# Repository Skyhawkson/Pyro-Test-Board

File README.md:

# Pyro-Test-Board
An analog, high-current pyrotechnic driver for evaluating high power rocketry igniters

This board is intended to evaluate igniters and other pyrotechnic devices used in high-power rocketry for safe parachute ejection. It uses closed-loop analog current control to drive a set current through a device of varying resistance while allowing for external measurements of the test device's performance. It is intended for benchtop use with a 3S or 4S LiPo battery, or a benchtop power supply. 

More information can be found in the [Schematic](https://github.com/Skyhawkson/Pyro-Test-Board/blob/main/Pyro%20Tester%20Rev1.0.0/Pyro%20Test%20Board.pdf) or the [KiCAD 7+ Project Files](https://github.com/Skyhawkson/Pyro-Test-Board/tree/main/Pyro%20Tester%20Rev1.0.0/Pyro%20Test%20Board%20Rev1.0.0).
SPICE simulation data is located in the [SPICE Sims](https://github.com/Skyhawkson/Pyro-Test-Board/tree/main/Pyro%20Tester%20Rev1.0.0/SPICE%20Sims) folder.

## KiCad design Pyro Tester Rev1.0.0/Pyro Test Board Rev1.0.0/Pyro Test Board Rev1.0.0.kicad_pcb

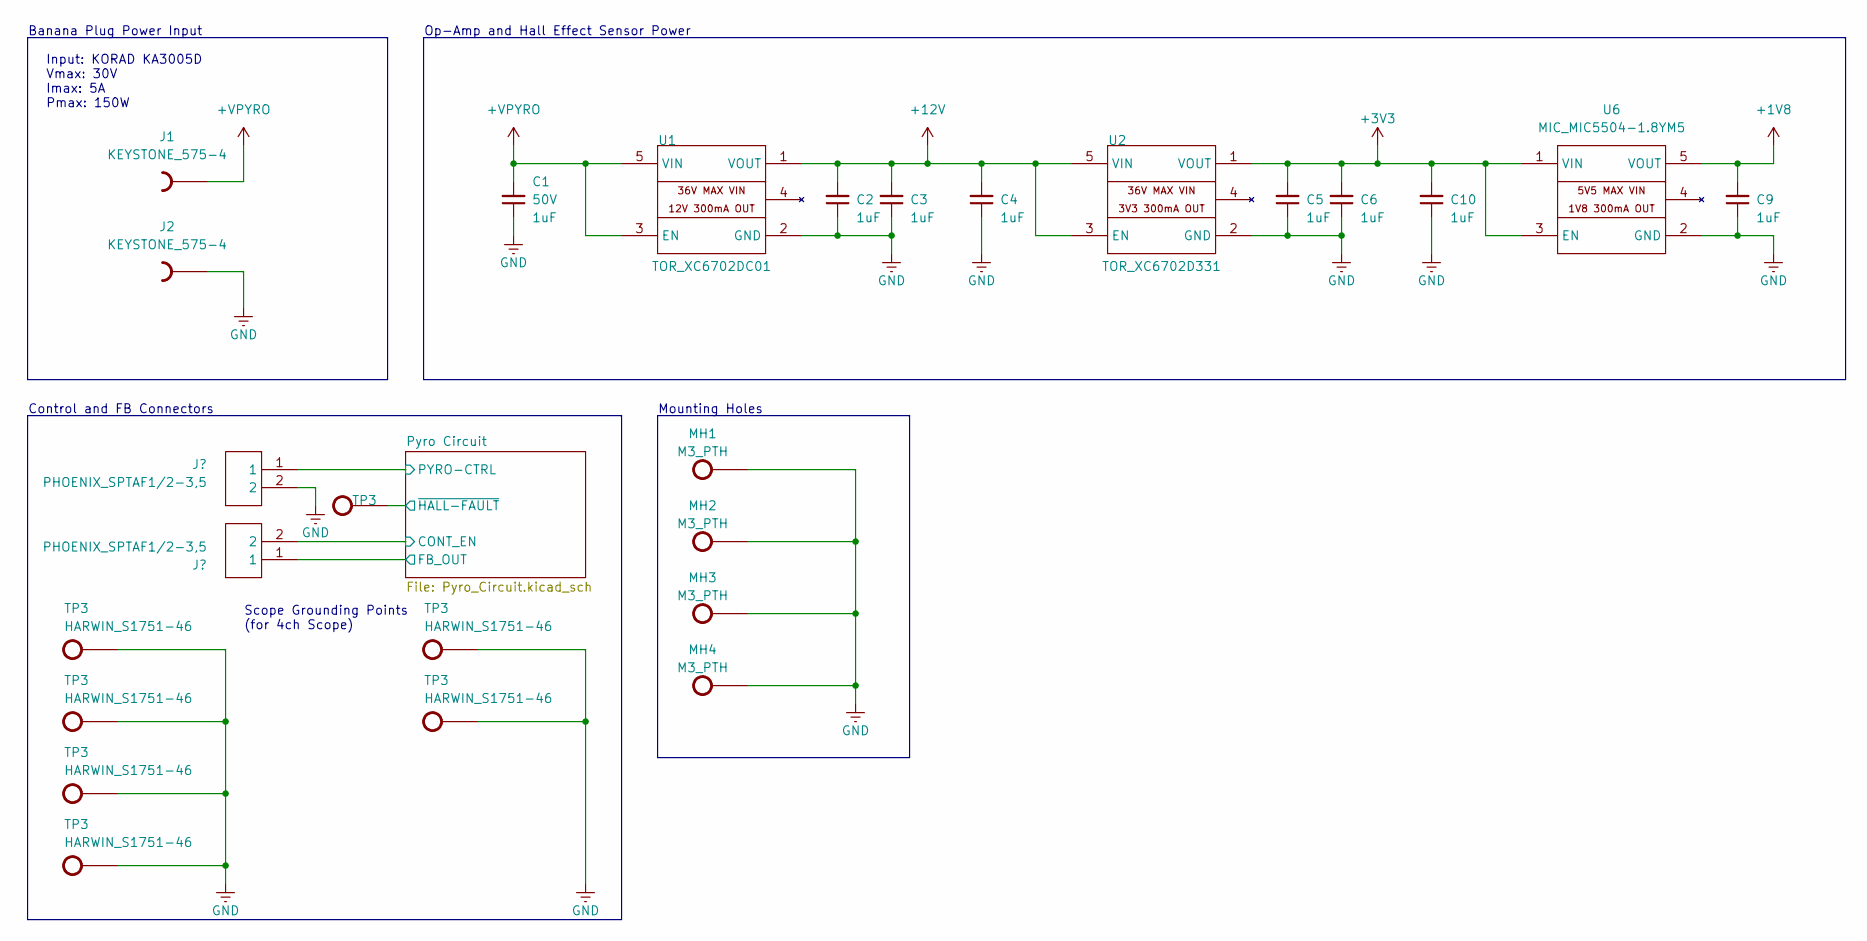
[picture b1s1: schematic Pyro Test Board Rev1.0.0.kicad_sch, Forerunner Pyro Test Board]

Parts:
C1, C2, C3, C4, C5, C6, C9, C10: 1UF_0805; GENERIC_0805_CAP; Tolerance 10%; Rating 50V
J1, J2: KEYSTONE_575-4
J3, J4: PHOENIX_SPTAF1/2-3,5; PHOENIX_SPTAF1_2-3,5
MH1, MH2, MH3, MH4: M3_PTH; GENERIC_MH_M3
TP3: HARWIN_S1751-46; HARWIN_S1751-XX
U1: TOR_XC6702DC01; TOR_SOT-89-5
U2: TOR_XC6702D331; TOR_SOT-89-5
U6: MIC_MIC5504-1.8YM5; MIC_SOT23-5LD-PL-1

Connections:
+1V8: C9.2, U6.5 (VOUT); also elsewhere on the board
+3V3: C5.2, C6.2, C10.2, U2.1 (VOUT), U6.1 (VIN), U6.3 (EN); also elsewhere on the board
+12V: C2.2, C3.2, C4.2, U1.1 (VOUT), U2.3 (EN), U2.5 (VIN); also elsewhere on the board
+VPYRO: C1.2, J1.1, U1.3 (EN), U1.5 (VIN); also elsewhere on the board
/Pyro Circuit/CONT_EN: J4.2, J4.2B; also elsewhere on the board
/Pyro Circuit/FB_OUT: J4.1, J4.1B; also elsewhere on the board
/Pyro Circuit/PYRO-CTRL: J3.1, J3.1B; also elsewhere on the board
GND: C1.1, C2.1, C3.1, C4.1, C5.1, C6.1, C9.1, C10.1, J2.1, J3.2, J3.2B, MH1.1, MH2.1, MH3.1, MH4.1, TP3.1, U1.2 (GND), U2.2 (GND), U6.2 (GND); also elsewhere on the board

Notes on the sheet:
Scope Grounding Points (for 4ch Scope)
Input: KORAD KA3005D Vmax: 30V Imax: 5A Pmax: 150W
Control and FB Connectors
Mounting Holes
Op-Amp and Hall Effect Sensor Power
Banana Plug Power Input

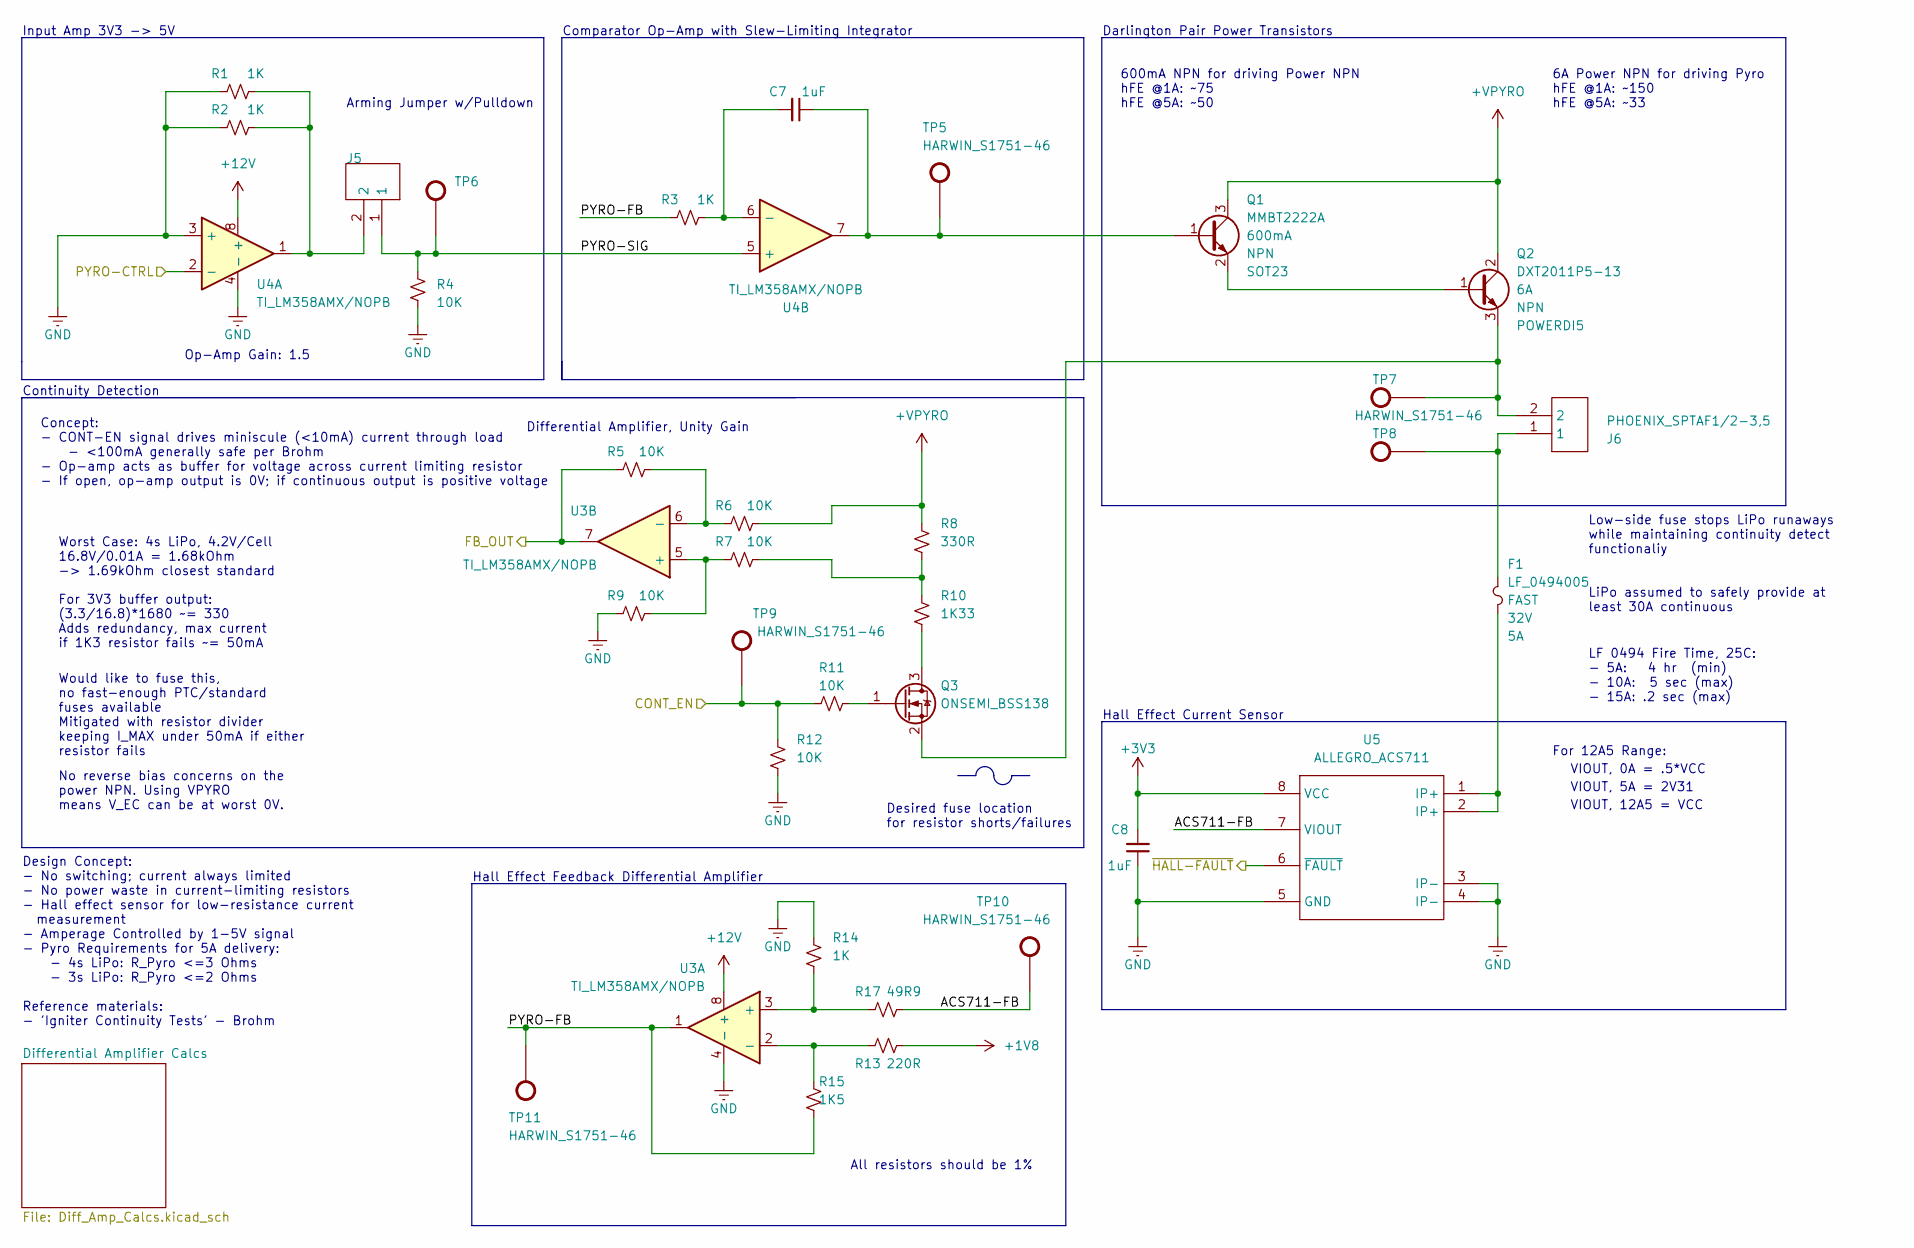
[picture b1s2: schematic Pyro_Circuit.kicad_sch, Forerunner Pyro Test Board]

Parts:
C7, C8: 1UF_0805; GENERIC_0805_CAP; Tolerance 10%; Rating 50V
F1: LF_0494005; LF_0494_(0603); VOLTAGE 32V
J5, J6: PHOENIX_SPTAF1/2-3,5; PHOENIX_SPTAF1_2-3,5
Q1: MMBT2222A; GENERIC_SOT-23
Q2: DXT2011P5-13; DIODES_POWERDI5
Q3: ONSEMI_BSS138; GENERIC_SOT-23
R1, R2, R3: 1K_0603; GENERIC_0603_RES; Tolerance 1%
R4, R5, R6, R7, R9, R11, R12: 10K_0603; GENERIC_0603_RES; Tolerance 1%
R8, R10: 1K33_0603; GENERIC_0603_RES; Tolerance 1%
R13: 220R_0603; GENERIC_0603_RES; Tolerance 1%
R14: 2K2_0603; GENERIC_0603_RES; Tolerance 5%
R15: 0R_0603; GENERIC_0603_RES; Tolerance 1%
R17: 49R9_0603; GENERIC_0603_RES; Tolerance 1%
TP5, TP6, TP7, TP8, TP9, TP10, TP11: HARWIN_S1751-46; HARWIN_S1751-XX
U3, U4: TI_LM358AMX/NOPB; TI_D0008A_(SOIC-8)
U5: ALLEGRO_ACS711; ALLEGRO_LC_(SOIC-8)

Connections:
+1V8: R13.2; also elsewhere on the board
+3V3: C8.2, U5.8 (VCC); also elsewhere on the board
+12V: U3.8 (+), U4.8 (+); also elsewhere on the board
+VPYRO: Q1.3 (C), Q2.2 (C), R6.2, R8.2; also elsewhere on the board
/Pyro Circuit/ACS711-FB: R17.2, TP10.1, U5.7 (VIOUT)
/Pyro Circuit/CONT_EN: R11.2, R12.2, TP9.1; also elsewhere on the board
/Pyro Circuit/FB_OUT: R5.1, U3.7; also elsewhere on the board
/Pyro Circuit/PYRO-CTRL: U4.2 (-); also elsewhere on the board
/Pyro Circuit/PYRO-FB: R3.1, R15.2, TP11.1, U3.1
/Pyro Circuit/PYRO-SIG: J5.1, J5.1B, R4.2, TP6.1, U4.5 (+)
/Pyro Circuit/~HALL-FAULT: U5.6 (~FAULT); also elsewhere on the board
GND: C8.1, R1.1, R2.1, R4.1, R9.1, R12.1, R14.2, U3.4 (-), U4.3 (+), U4.4 (-), U5.3 (IP-), U5.4 (IP-), U5.5 (GND); also elsewhere on the board
unnamed: F1.1, U5.1 (IP+), U5.2 (IP+)
unnamed: F1.2, J6.1, J6.1B, TP8.1
unnamed: J5.2, J5.2B, R1.2, R2.2, U4.1
unnamed: C7.1, Q1.1 (B), TP5.1, U4.7
unnamed: Q1.2 (E), Q2.1 (B)
unnamed: J6.2, J6.2B, Q2.3 (E), Q3.2 (S), TP7.1
unnamed: Q3.3 (D), R10.1
unnamed: Q3.1 (G), R11.1
unnamed: R7.2, R8.1, R10.2
unnamed: R13.1, R15.1, U3.2 (-)
unnamed: R14.1, R17.1, U3.3 (+)
unnamed: R7.1, R9.2, U3.5 (+)
unnamed: R5.2, R6.1, U3.6 (-)
unnamed: C7.2, R3.2, U4.6 (-)

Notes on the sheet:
Hall Effect Current Sensor
All resistors should be 1%
600mA NPN for driving Power NPN hFE @1A: ~75 hFE @5A: ~50
Differential Amplifier, Unity Gain
Arming Jumper w/Pulldown
Would like to fuse this, no fast-enough PTC/standard fuses available Mitigated with resistor divider keeping I_MAX under 50mA if either resistor fails
Design Concept: - No switching; current always limited - No power waste in current-limiting resistors - Hall effect sensor for low-resistance current measurement - Amperage Controlled by 1-5V signal - Pyro Requirements for 5A delivery: - 4s LiPo: R_Pyro <=3 Ohms - 3s LiPo: R_Pyro <=2 Ohms Reference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
For 12A5 Range:
VIOUT, 5A = 2V31
6A Power NPN for driving Pyro hFE @1A: ~150 hFE @5A: ~33
Desired fuse location for resistor shorts/failures
Worst Case: 4s LiPo, 4.2V/Cell 16.8V/0.01A = 1.68kOhm -> 1.69kOhm closest standard
VIOUT, 12A5 = VCC
Darlington Pair Power Transistors
Continuity Detection
LF 0494 Fire Time, 25C: - 5A: 4 hr (min) - 10A: 5 sec (max) - 15A: .2 sec (max)
Comparator Op-Amp with Slew-Limiting Integrator
No reverse bias concerns on the power NPN. Using VPYRO means V_EC can be at worst 0V.
For 3V3 buffer output: (3.3/16.8)*1680 ~= 330 Adds redundancy, max current if 1K3 resistor fails ~= 50mA
Low-side fuse stops LiPo runaways while maintaining continuity detect functionaliy LiPo assumed to safely provide at least 30A continuous
Input Amp 3V3 -> 5V
Op-Amp Gain: 1.5
Concept: - CONT-EN signal drives miniscule (<10mA) current through load - <100mA generally safe per Brohm - Op-amp acts as buffer for voltage across current limiting resistor - If open, op-amp output is 0V; if continuous output is positive voltage
Hall Effect Feedback Differential Amplifier
VIOUT, 0A = .5*VCC

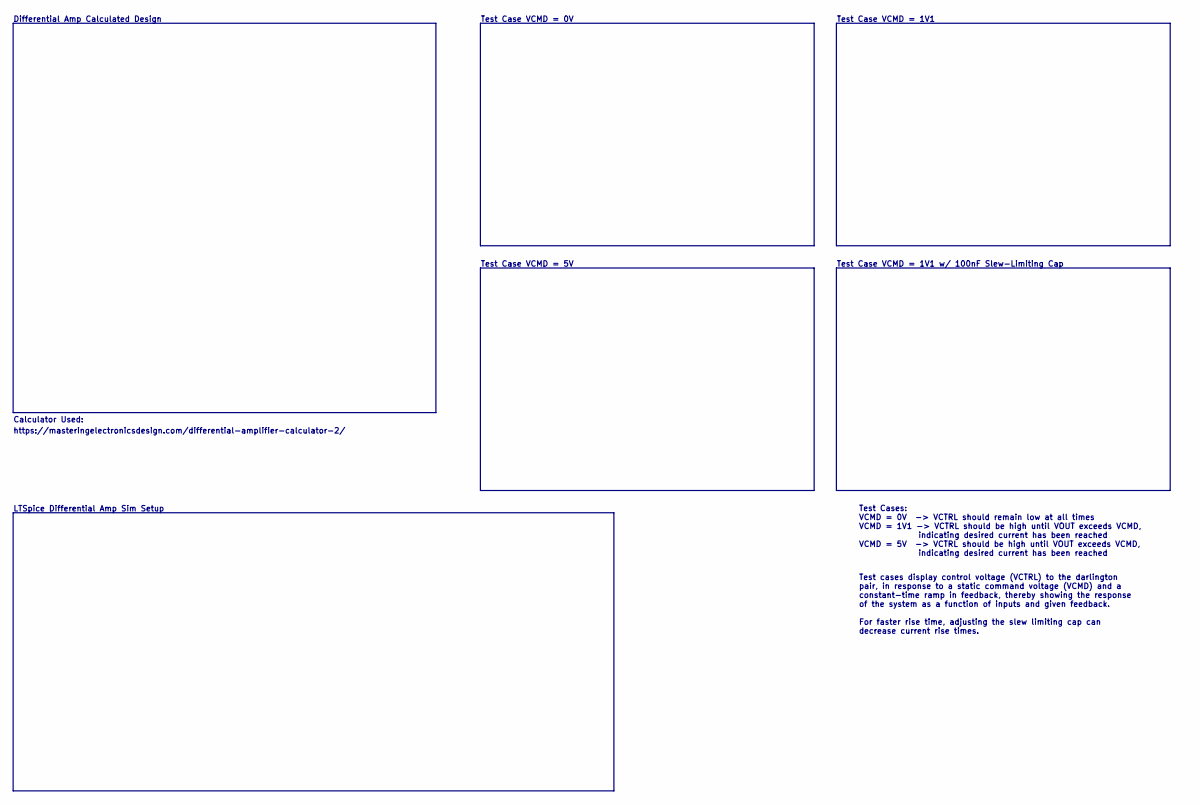
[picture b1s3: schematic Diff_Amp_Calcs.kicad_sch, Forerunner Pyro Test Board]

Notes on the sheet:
Test Case VCMD = 1V1
Test Case VCMD = 1V1 w/ 100nF Slew-Limiting Cap
Test Cases: VCMD = 0V -> VCTRL should remain low at all times VCMD = 1V1 -> VCTRL should be high until VOUT exceeds VCMD, indicating desired current has been reached VCMD = 5V -> VCTRL should be high until VOUT exceeds VCMD, indicating desired current has been reached
Test Case VCMD = 5V
Calculator Used:
Test Case VCMD = 0V
Differential Amp Calculated Design
https://masteringelectronicsdesign.com/differential-amplifier-calculator-2/
LTSpice Differential Amp Sim Setup
Test cases display control voltage (VCTRL) to the darlington pair, in response to a static command voltage (VCMD) and a constant-time ramp in feedback, thereby showing the response of the system as a function of inputs and given feedback. For faster rise time, adjusting the slew limiting cap can de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

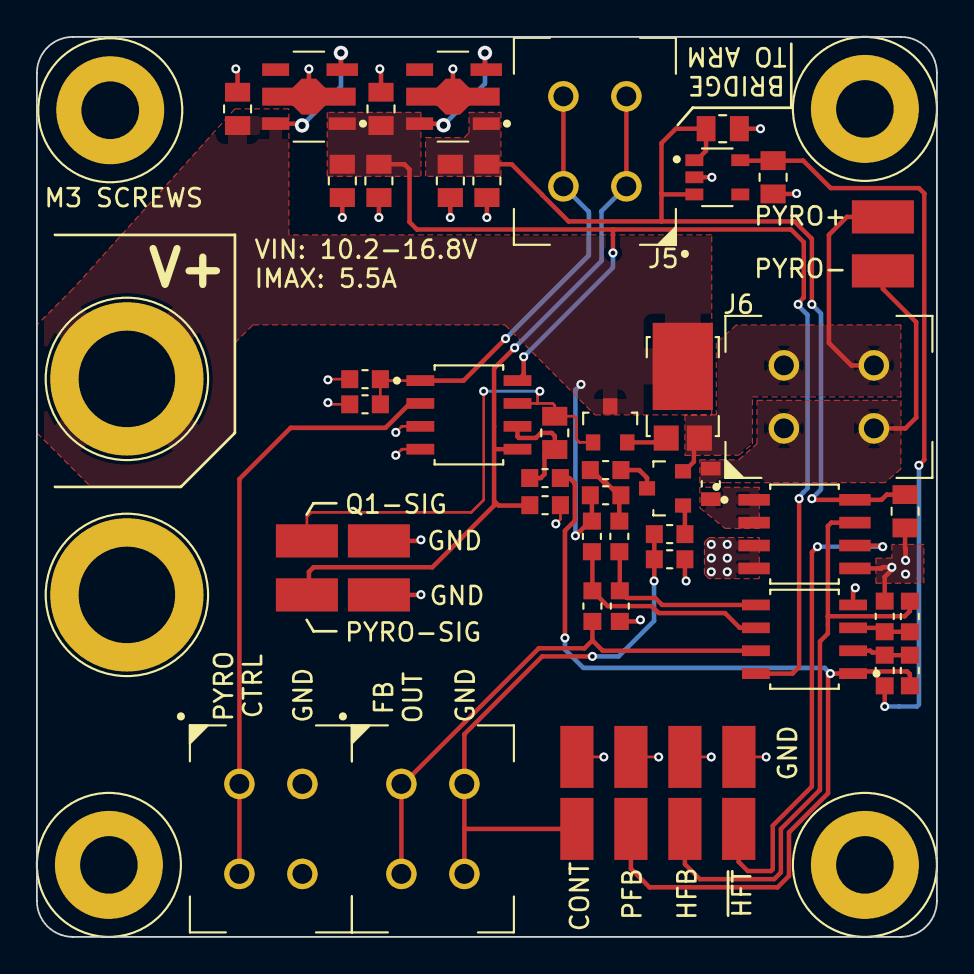
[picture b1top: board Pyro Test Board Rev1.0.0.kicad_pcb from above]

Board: 2 copper layers, 50.0 x 50.0 mm, 60 parts (0 on the bottom side), 26 nets.

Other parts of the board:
TP1, TP2, TP4, TP12, TP13, TP14: HARWIN_S1751-46; HARWIN_S1751-XX

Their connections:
/Pyro Circuit/~HALL-FAULT: TP12.1; also elsewhere on the board
GND: TP1.1, TP2.1, TP4.1, TP13.1, TP14.1; also elsewhere on the board

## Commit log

2024-02-06 Added Rev1.0.0 Release Files
    Rev1.0.0 was completed in another repository before being broken off into its own
